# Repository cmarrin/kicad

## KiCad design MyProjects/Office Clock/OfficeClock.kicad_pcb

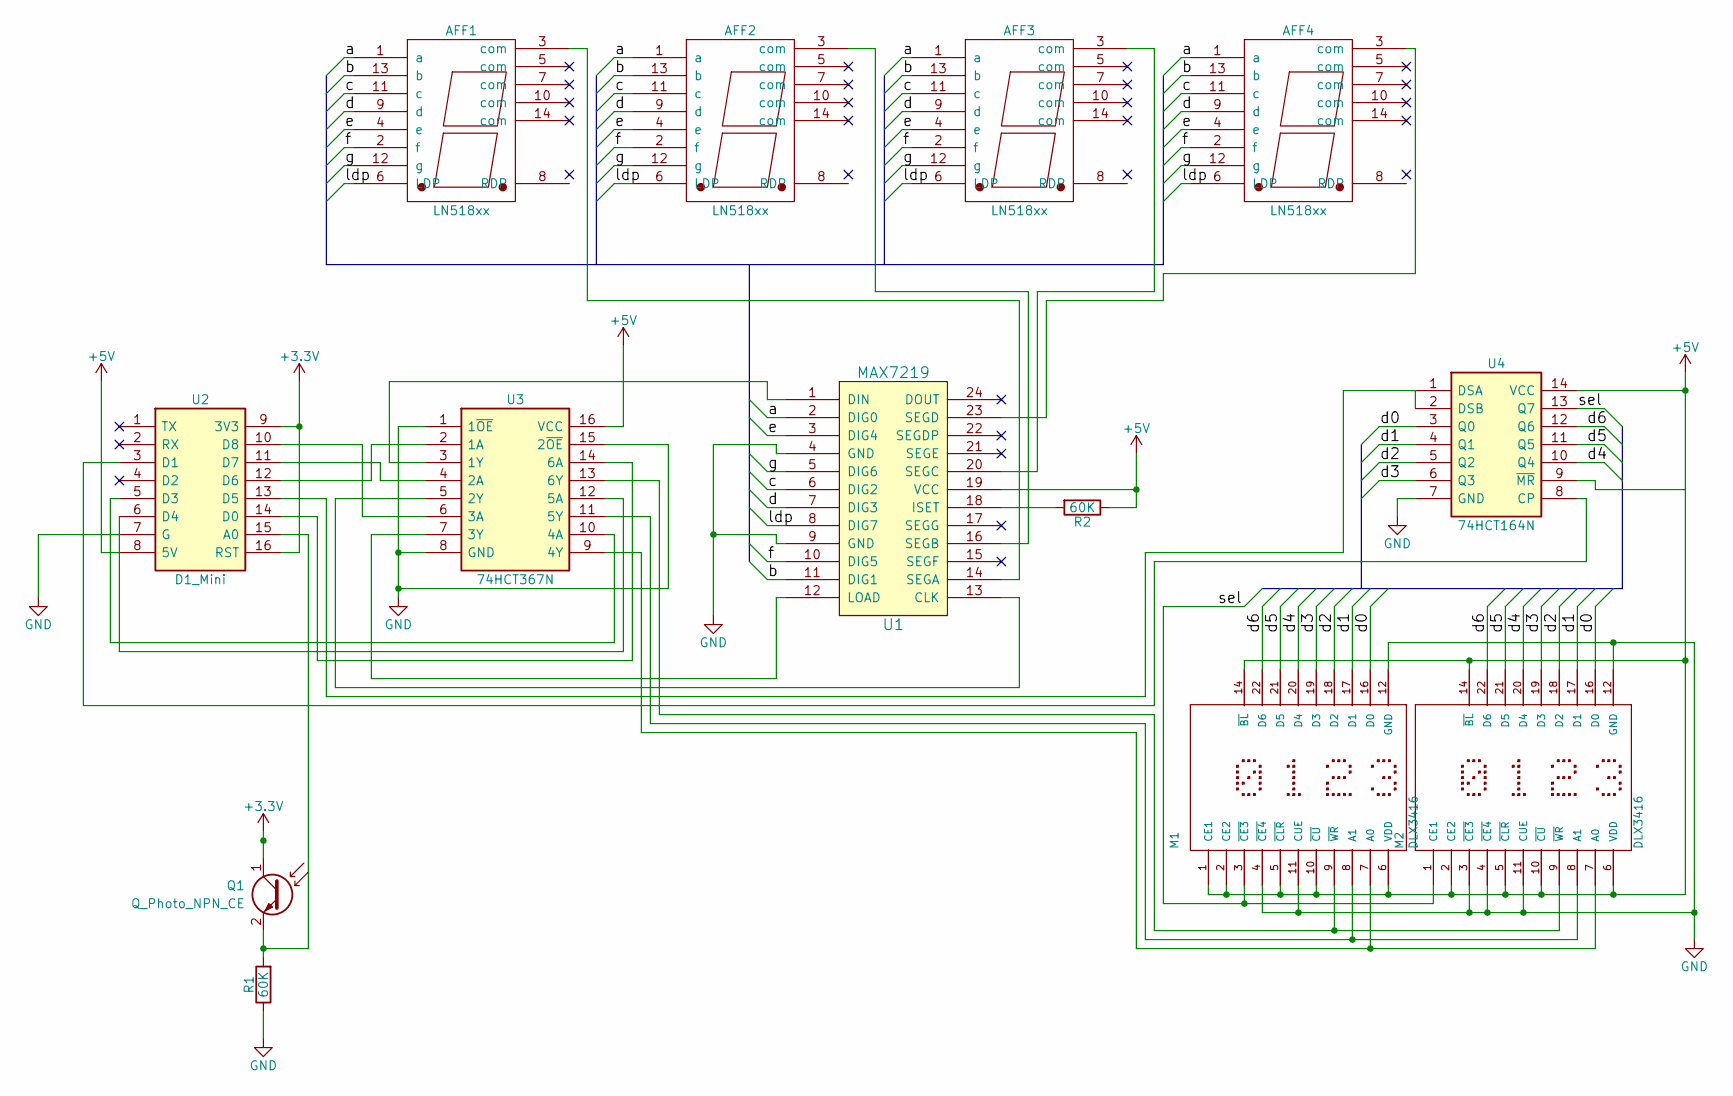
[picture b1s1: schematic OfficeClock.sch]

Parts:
AFF1, AFF2, AFF3, AFF4: LN518xx
M1, M2: DLX3416; DLX3416-DLX3416
Q1: Q_Photo_NPN_CE; PhotoTransistor_Osram_LPT80A
R1, R2: 60K; R_Axial_DIN0207_L6.3mm_D2.5mm_P10.16mm_Horizontal
U1: MAX7219; DIP-24_W7.62mm_LongPads
U2: D1_Mini; D1-MINI; Manufacturer_Part_Number D1 Mini
U3: 74HCT367N; DIP-16_W7.62mm_LongPads; Manufacturer_Part_Number 74HCT367N
U4: 74HCT164N; DIP-14_W7.62mm_LongPads; Manufacturer_Part_Number 74HCT164N

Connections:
+3V3: Q1.1 (C), U2.9 (3V3), U2.16 (RST)
+5V: M1.1 (CE1), M1.2 (CE2), M1.5 (~CLR), M1.6 (VDD), M1.10 (~CU), M1.14 (~BL), M2.2 (CE2), M2.5 (~CLR), M2.6 (VDD), M2.10 (~CU), M2.14 (~BL), R2.1, U1.19 (VCC), U2.8 (5V), U3.16 (VCC), U4.14 (VCC)
/a: AFF1.1 (a), AFF2.1 (a), AFF3.1 (a), AFF4.1 (a), U1.2 (DIG0)
/b: AFF1.13 (b), AFF2.13 (b), AFF3.13 (b), AFF4.13 (b), U1.11 (DIG1)
/c: AFF1.11 (c), AFF2.11 (c), AFF3.11 (c), AFF4.11 (c), U1.6 (DIG2)
/d: AFF1.9 (d), AFF2.9 (d), AFF3.9 (d), AFF4.9 (d), U1.7 (DIG3)
/d0: M1.16 (D0), M2.16 (D0), U4.3 (Q0)
/d1: M1.17 (D1), M2.17 (D1), U4.4 (Q1)
/d2: M1.18 (D2), M2.18 (D2), U4.5 (Q2)
/d3: M1.19 (D3), M2.19 (D3), U4.6 (Q3)
/d4: M1.20 (D4), M2.20 (D4), U4.10 (Q4)
/d5: M1.21 (D5), M2.21 (D5), U4.11 (Q5)
/d6: M1.22 (D6), M2.22 (D6), U4.12 (Q6)
/e: AFF1.4 (e), AFF2.4 (e), AFF3.4 (e), AFF4.4 (e), U1.3 (DIG4)
/f: AFF1.2 (f), AFF2.2 (f), AFF3.2 (f), AFF4.2 (f), U1.10 (DIG5)
/g: AFF1.12 (g), AFF2.12 (g), AFF3.12 (g), AFF4.12 (g), U1.5 (DIG6)
/ldp: AFF1.6 (LDP), AFF2.6 (LDP), AFF3.6 (LDP), AFF4.6 (LDP), U1.8 (DIG7)
/sel: M1.3 (~CE3), M2.1 (CE1), U4.13 (Q7)
GND: M1.4 (~CE4), M1.11 (CUE), M1.12 (GND), M2.3 (~CE3), M2.4 (~CE4), M2.11 (CUE), M2.12 (GND), R1.1, U1.4 (GND), U1.9 (GND), U2.7 (G), U3.1 (1~OE), U3.8 (GND), U3.15 (2~OE), U4.7 (GND)
unnamed: AFF1.3 (com), U1.14 (SEGA)
unnamed: AFF2.3 (com), U1.16 (SEGB)
unnamed: AFF3.3 (com), U1.20 (SEGC)
unnamed: AFF4.3 (com), U1.23 (SEGD)
unnamed: M1.7 (A0), M2.7 (A0), U3.9 (4Y)
unnamed: M1.8 (A1), M2.8 (A1), U3.11 (5Y)
unnamed: M1.9 (~WR), M2.9 (~WR), U3.13 (6Y)
unnamed: Q1.2 (E), R1.2, U2.15 (A0)
unnamed: R2.2, U1.18 (ISET)
unnamed: U1.1 (DIN), U3.3 (1Y)
unnamed: U1.12 (LOAD), U3.7 (3Y)
unnamed: U1.13 (CLK), U3.5 (2Y)
unnamed: U2.3 (D1), U4.8 (CP)
unnamed: U2.5 (D3), U3.10 (4A)
unnamed: U2.6 (D4), U3.12 (5A)
unnamed: U2.10 (D8), U3.6 (3A)
unnamed: U2.11 (D7), U3.4 (2A)
unnamed: U2.12 (D6), U3.2 (1A)
unnamed: U2.13 (D5), U4.1 (DSA), U4.2 (DSB)
unnamed: U2.14 (D0), U3.14 (6A)

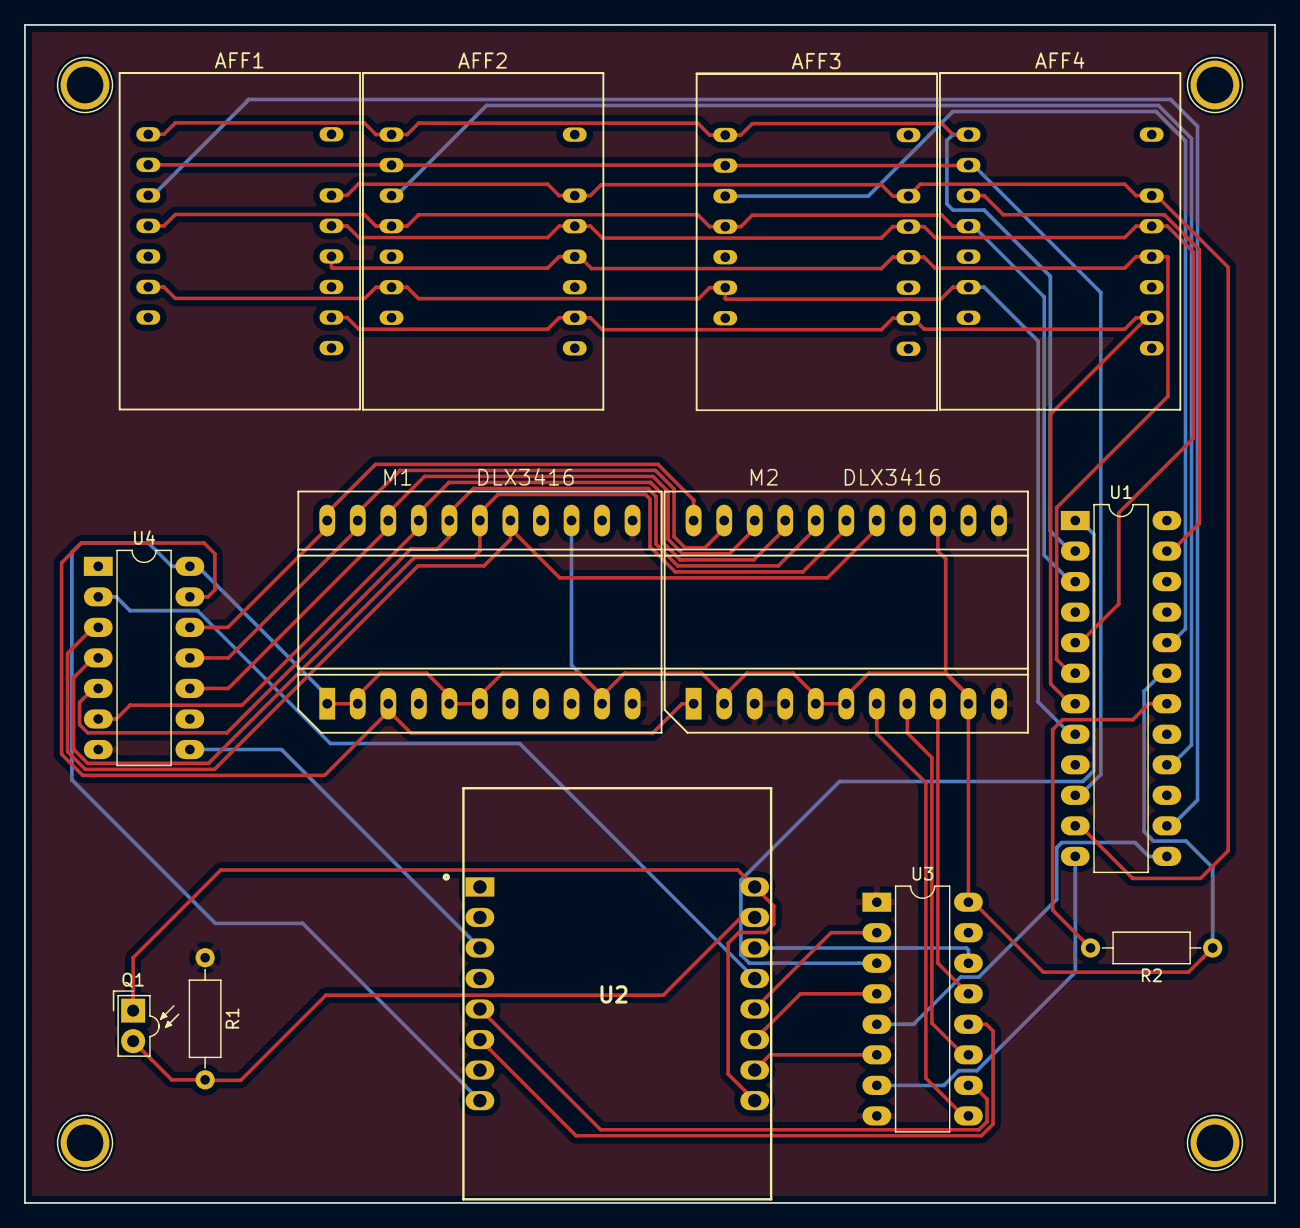
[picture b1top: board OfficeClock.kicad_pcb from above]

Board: 2 copper layers, 104.0 x 98.0 mm, 13 parts (0 on the bottom side), 39 nets.

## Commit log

2017-12-20 initial commit of Office Clock files
2017-12-21 Finished schematic wiring
2017-12-21 Finished laying out board with filled zones
2017-12-23 Finished laying out 2 sided PCB with fill
2017-12-23 Got rid of Space in Office Clock name
2017-12-23 Changed name of project folder to OfficeSpace without a space
